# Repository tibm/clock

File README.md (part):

# Wooden Smart Clock — Hardware Specification

> Living spec for a high-quality, low-power desk alarm clock: a **walnut cube (~120 mm)** with an **aluminum front plate**, a centered **Ø~90 mm MCU-driven analog dial behind glass** (aluminum hands on walnut, 12 black hour dots, no numerals), a row of **5 RGBW status LEDs** under the dial, and one **aluminum knob (rotate + press)** centered on the top face.

> 🔩 **Manufacturing constraint — HAND-SOLDERABLE PARTS ONLY.** The bare PCB is fab'd externally; **every part is hand-soldered with an iron.** No **QFN / DFN / WSON / BGA / WLP / LGA** silicon sits bare on the board — every active IC is a **leaded/gullwing** package (SOIC / SOP / SSOP / TSSOP / **HTSSOP** / **MSOP** / SOT-23) or a **castellated/edge module**. The two power parts (amp `TAS5760M`, charger `LT3652`) are HTSSOP/MSOP **PowerPAD** — leads iron-solderable, belly pad on a thermal-via array (back-side hot-air optional). Functions that *only* exist leadless → **pre-made breakout modules** (env/MEMS sensors — **BME688, TSL2591, BNO085** as I²C Qwiic/STEMMA boards; or a custom SMT daughterboard — **built: [`kicad-sensor/`](kicad-sensor/), `SENSE v0.2`**, §8) or **dropped** (fuel gauge → ESP32 ADC). **Passives ≥ 0603** (0402 min); connectors hand-solderable (through-hole / wide-pad SMD: USB-C, FPC/ZIF, JST, SD cage). **This grows the PCB — accepted.**

**Status:** v0.19 draft · **Owner:** you (FW/HW) · **Last updated:** 2026-07-19 · **What is left to build: [`TODO.md`](TODO.md)** · clock ⇄ app protocol: [`app/PROTOCOL.md`](app/PROTOCOL.md)

**Changelog**
- v0.19 — **Product redesign: walnut cube + aluminum face — display dropped, NeoPixel status/face LEDs + top-knob UX added (2026-07-19).** New form (§3): perfect **walnut cube ~120 mm** (size flexible, larger eases manufacturing), all faces wood except an **aluminum front plate** (cube − 10 mm in W/H, flush-centered → **5 mm wood reveal**) with a **centered Ø~90 mm dial opening** behind glass — **aluminum hands over a walnut dial**, no numerals, **12 black hour dots**; below the opening, **5 status-LED holes + icons** (Lucide-style `bell`, `alarm-clock`, `clock`, `volume-1`, `battery`); an **aluminum knob (rotary + push)** perfectly centered on the top face; wake light, speaker openings and USB port on the **back**. Consequences: **(1) Sharp LS032B7DD02 + FH34 FPC connector dropped** (§4; their datasheets stay in [`/datasheet`](datasheet/) for possible future reuse) — SPI2 is now **microSD-only**, software-VCOM notes moot, `LCD_DISP`/`LCD_CS` freed. **(2) Panel-LED string dropped** (Cree CLM3C ×≤12 + its AO3400A + one LEDC channel recovered) → **7× SK6812 RGBW NeoPixels on the PCB** ([Adafruit 2758](https://www.digikey.com/en/products/detail/adafruit-industries-llc/2758/6134706), 10-pack $5.95): **5 status + 2 dial-illumination**, chained on the **5 V rail** (works on battery) behind **one data GPIO (IO7 → RMT)** through an **SN74AHCT1G125 3.3→5 V buffer** ([DigiKey 376028](https://www.digikey.com/en/products/detail/texas-instruments/SN74AHCT1G125DBVR/376028), $0.14). **(3) UI = single knob**: Bourns **EM14A0D-C24-L064S** **optical** encoder (**no detent, 64 CPR**, integral push switch, **5 V** opto-ASIC, [DigiKey 954403](https://www.digikey.com/en/products/detail/bourns-inc/EM14A0D-C24-L064S/954403), $34.00) under a Kilo **OEJNI-90-1-5** machined aluminum knob (Ø23.5 mm, 1/4″ bore + set screw = the encoder's 1/4″ flatted shaft, [DigiKey 5970396](https://www.digikey.com/en/products/detail/kilo-international/OEJNI-90-1-5/5970396), $13.43), off-board on J10 (JST **ZH** 1×06 B6B-ZR incl. **+5 V** — same family + pre-crimped A06ZR cable as the sensor board) → **A/B are 5 V outputs → 100k/200k dividers → IO47/48 (PCNT)**, **ENC_SW moved MCP23017 → host IO17** (freed by the display) for a tight-debounce interrupt; **rear tactiles BTN1–3 dropped**, one **radio-disable toggle** remains on the expander (GPA3) via **J11** (JST ZH 1×02). **(4) USB-C receptacle → vertical GCT USB4160-03-0230-C** (24-pin USB 3.2 Gen2 vertical, of which only the **USB 2.0 subset** — VBUS/GND/**CC/D±** — is wired, SS pads unconnected → native USB-JTAG + 15 V PD intact; [DigiKey](https://www.digikey.com/en/products/result?keywords=USB4160-03-0230-C), **$1.22, 5,753 in stock**, active) standing on the PCB, port exits the back wall directly — **USB4105 + Adafruit 6069 panel extension dropped**; footprint adapted into `kicad/clock.pretty` from the user-supplied vendor CAD file. *(Vetting trail: **USB4140** rejected = 6-pin power-only, no D±; **UJ20-C-V-C-1** rejected = legs/layout specified for a 0.8 mm PCB; **UJ20-C-V-C-2** (TH, $0.95) was briefly primary but is backorder-only; **USB4145-03-0170-C** ($1.05) remains a same-land-family 16-pin alt.)* **(5) Orientation-awareness (R14) retired** (the cube is fixed upright; LIS3DH stays for tap-to-snooze). Unchanged: wake COB (12 V, plugged-only), audio chain, charger + battery safety, sensors, homing, steppers. Schematic (`kicad/`) regenerated; docs synced.
- v0.18 — **Protector re-picked (AP9101C went NRND/obsolete) → HYCON HY2111-GB** (SOT-23-6, OV 4.28 V / OD 2.90 V, pin-arrangement-identical → same nets; support values per its datasheet: R VDD 330 Ω→**100 Ω**, R CS 2.7 k→**2 kΩ**; AOSD32334C dual-FET unchanged). Quality single-qty alternatives (ABLIC S-8261ABMMD, Nisshinbo R5478N) are reel-only/no-stock at DigiKey → HY2111-GB sourced **LCSC C82747** (off-DigiKey like the CH224K). **X40.879 mounts directly on the PCB**: custom KiCad footprint + symbol drawn from the factory STEP + pinout figure (8 solder pins, Ø10 shaft clearance hole, both shafts pass through the board); **J4 stepper connector dropped**. **USB-C port moved to the enclosure wall** via the Adafruit **6069** panel-mount **extension** ([DigiKey 25897275](https://www.digikey.com/en/products/detail/adafruit-industries-llc/6069/25897275), ~$4.50) — the on-board **USB4105** receptacle + CH224K stay unchanged (a passive C-plug→panel-C-jack passthrough keeps CC/PD intact; the resistor-equipped Adafruit 6153 pigtail was rejected — its built-in 5.1 kΩ CC pull-downs would break the 15 V PD contract). Datasheets: `battery_protector_ap9101c.pdf` → `battery_protector_hy2111.pdf`. Schematic (`kicad/`) regenerated; docs synced.
- v0.17 — **Homing sensor re-picked: Everlight ITR8307 (went unavailable) → onsemi QRE1113.** Same reflective **phototransistor with analog output → 1 ADC pin**, so it drops into the **same 150 Ω ballast / 10 kΩ load network** unchanged (§5, [`power_values.md`](power_values.md)); no firmware or pin-map change. Trade-off: the QRE1113 is **larger (≈3.6×2.9×1.7 mm** vs the ITR8307's 3.4×1.5×1.1 mm) → a marginally bigger dial hole — still far smaller than the dropped **TCND5000** (6×4.3×3.75 mm). Through-hole gull-wing `QRE1113` (SMD `QRE1113GR` alt), trivially hand-solderable, **DigiKey 2175990 (~$0.76)**. Synced §5/§8/§16b + block diagram + [`datasheet/README.md`](datasheet/README.md) (`sensor_homing_optical_itr8307.pdf` → `sensor_homing_QRE1113-D.PDF`).
- v0.16 — **LED 12 V source resolved · MCP23017 IO expander added · pin-level map (`esp32.md`) + schematic values (`power_values.md`) · backup mode / TCO / VCOM decided.** LED: **no barrel jack** — the wake COB runs off the shared **TPS55340 12 V boost, plugged-only**; on battery the amp PVDD auto-drops to the **5 V rail via an LTC4412 mux** (quieter alarm) and the 5 V panel LEDs stay on (§9/§10, [`led.md`](led.md)). **Added the Microchip MCP23017** I²C IO expander (SOIC/SSOP-28) on the shared bus to offload slow/static lines (SPK_SD, 12 V-boost EN, stepper STBY, buttons, encoder-switch, PD PG, charger CHRG/FAULT) → **net −7 host GPIO** (§6/§16b; datasheet §19). Full **pin map now in [`esp32.md`](esp32.md)** (native USB-JTAG on IO19/20, **software VCOM** with EXTMODE=L, shared display+SD on SPI2 → **32/33 module pads**), and **per-converter passive/FB/comp values in [`power_values.md`](power_values.md)**. Decisions (2026-07-12): **backup mode = adaptive** (Wi-Fi modem-sleep → deep-sleep at low SoC); **one-shot ~77 °C TCO added** to the cell path (§10); **software VCOM** locked. Corrected the 32.768 kHz load-cap value (**~18 pF**, was mis-stated). Synced [`datasheet/README.md`](datasheet/README.md), [`power.md`](power.md), [`CLAUDE.md`](CLAUDE.md).
- v0.15 — **Sensor set consolidated to 3 parts + hand-assembly path chosen (§8).** Dropped the redundant **TMP117** (any temp sensor already gives the reading); folded **SHT45 + SGP41 → one Bosch BME688** (T + RH + pressure + VOC/gas via BSEC — one chip, one board on the bus); accel **BMA400 → LIS3DH** (no leaded accel exists; low-res tap+gravity is all we need). **Locked set = BME688 + TSL2591 + LIS3DH on both build paths → firmware identical either way.** **Build = option 2a: a STEMMA QT / Qwiic daisy-chain** of three ready Adafruit boards on one 4-wire I²C chain — **BME688 (Adafruit 5046, ~$19) + TSL2591 (1980, $6.95) + LIS3DH (2809, $4.95)** — no leadless silicon touched by the iron. **Future option 2b:** the **same** three bare chips on one small custom daughterboard, JLCPCB SMT-assembled, hand-solder only its header → smallest footprint, same part numbers → same firmware. Filed `sensor_env_bme688.pdf` + `sensor_accel_lis3dh.pdf`; removed the now-unused TMP117/SHT4x/BMA400 datasheets. Synced §8/§16a/§16b + [`datasheet/README.md`](datasheet/README.md).
- v0.14 — **Homing reworked: 2× DRV5032 Hall + hand magnets → 1× reflective optical (Everlight ITR8307).** One sensor behind a **punched dial hole**, sequential per-shaft homing, **no hand magnets** (§5). Evaluated the longer-range **Vishay TCND5000** for a >3 mm hand stand-off and **dropped it** — at **6×4.3×3.75 mm** it's ~5× the ITR8307 footprint (**3.4×1.5×1.1 mm**) → a bigger dial hole; **ITR8307 locked for the smallest hole**, hands kept **<3 mm** off the dial. Synced §3/§5/§8/§16b/§17 + [`datasheet/README.md`](datasheet/README.md) (dropped the stale Hall rows; only `sensor_homing_optical_itr8307.pdf` filed).
- v0.13 — **RTC IC dropped → ESP32-S3 RTC + 32.768 kHz crystal (no battery).** A battery-less RTC chip loses time on total power loss exactly like the S3, so it adds parts without fixing anything; the S3's internal RC oscillator alone drifts %-level over temperature (bad for a clock). Fix = a ~30¢ **32.768 kHz watch crystal** on XTAL32K (GPIO15/16) → ±~20 ppm ≈ 1.7 s/day, disciplined by **SNTP**. On loss of USB **and** the 18650, time is lost → re-sync on boot with a clock animation (accepted). Removed the RV-3028-C7/DS3231SN row + datasheet; §8, §16, §17, §6c synced.
- v0.12 — **Sensors, display connector & RTC finalized to precise parts + datasheets** ([`/datasheet`](datasheet/) rows 11–16): display FPC → **Hirose FH34SRJ-10S-0.5SH** (10-pin 0.5 mm ZIF, the panel spec's own recommended mate, on-board); T/RH → **SHT45** (±0.1 °C / ±1 %RH, replaces SHT40) + optional dedicated **TMP117** (±0.1 °C); light → **TSL2591** (188 µlx–88 klx, weak-light, replaces VEML7700); accel+orient → **BMA400** (now datasheeted); RTC **kept = RV-3028-C7** (ULP 45 nA) / **DS3231SN** (SOIC-16, on-board) — the S3's internal RTC dies on full power loss, so a backed-up RTC gives instant-correct hands at cold boot + holdover. Production BOM (§16b), §8 sensor table, and [`datasheet/README.md`](datasheet/README.md) synced; leadless sensors ride on I²C breakouts, the FPC connector is on-board.
- v0.11 — **Hand-solderable parts only (hard mfg constraint):** every bare-PCB IC is now a leaded package — no QFN/DFN/BGA/LGA. Swaps: amp **TAS5825M (VQFN) → TAS5760M** (HTSSOP-32, I²S+I²C; HPF/limiter DSP moves to firmware); driver **2× DRV8835 (WSON) → 2× TB6612FNG** (SSOP-24); PD **STUSB4500 (QFN) → CH224K** (ESSOP-10, resistor-set, off-DigiKey); charger **BQ25628E (WQFN) → LT3652** (MSOP-12E buck, BAT-node power-path, resistor-set 4.05 V + NTC + timer — no I²C, single-window temp); **fuel gauge MAX17048 (µDFN) dropped → ESP32 ADC**; protector **LC05111 (DFN) → S-8261 (SOT-23-6) + AO4800 dual-FET (SO-8)**. Leadless-only env sensors → **I²C breakout modules**. New top-of-file mfg note; datasheets swapped in [`/datasheet`](datasheet/); board grows — accepted.
- v0.10 — **Power/safety simplified (Option A)**: buck-boost **BQ25792 → BQ25628E** (1-cell buck charger, integrated FETs — buck is enough since input always > 1S cell); independent **cell protector = onsemi LC05111** (integrated FET) + **reverse-polarity P-FET** + NTC/JEITA + TVS = **double-redundant, industry-standard for 1S**. Dropped BQ29700+FETs, **secondary OVP, one-shot TCO, PPTC** (over-engineering for a single cell). Datasheets added (STUSB4500, BQ25628E, MAX17048, LC05111); `power.md` now has a **How-to-use / bring-up** section. Power subtotal ~$23 → ~$15.
- v0.9 — **Power tree locked** ([`power.md`](power.md)): **USB-PD sink (STUSB4500, 15 V)** → **BQ25792** buck-boost charger/path (+ MAX17048), 1S. Rails 3.3 / 5 / 12 V-audio-boost / 15 V-VBUS-LED. Battery = **user-supplied 18650 in a holder, Li-ion ONLY (labeled)**; **48 h backup**; health-cap ~80 %. **Mandatory board safety for any 18650**: reverse-polarity (LM74700-Q1), primary PCM (BQ29700+FETs), redundant secondary OVP, PPTC + thermal cutoff, NTC/JEITA, TVS, FR barrier — triple-redundant overcharge, layered over-discharge. Charger BQ25185 → **BQ25792**; §10/§16/§17 updated.
- v0.8 — **Amp locked = TI TAS5825M** (I²S + I²C closed-loop Class-D w/ DSP), PBTL mono into the 4 Ω DMA58-4: PVDD 5 V for ~3 W, optional ~12 V boost for ~8–12 W; DSP loads a ~150–180 Hz high-pass + limiter to protect the 2 mm-Xmax driver. MAX98357A demoted to simple/no-DSP alt. **Driver confirmed = 2× TI DRV8835** (dual H-bridge each; VM 5 V for full torque, VCC 3.3 V; PHASE/ENABLE with PWM microstep → 8 GPIO). Full datasheets added to [`/datasheet`](datasheet/); [`datasheet/README.md`](datasheet/README.md) now carries a **System IO & power domains** table (rails + per-part GPIO/voltage).
- v0.7 — **Speaker PC68-4 → Dayton DMA58-4** (2″ dual-magnet full-range — the driver we actually have a datasheet for) → smaller driver relaxes body depth to **≥45–60 mm / ~100–250 cc** chamber (optional **DMA58-PR** passive radiator for bass). **Movement locked = Juken X40.879**: its datasheet is a short **pinout addendum** that defers to the **X27 base spec** for torque/current/dimensions — both now in [`/datasheet`](datasheet/). Added the **full Sharp LS032B7DD02 device spec** (replaced the marketing brief); corrected display **active area → 42.67 × 68.07 mm** and **power → 30 µW hold / 250 µW update @ 5 V (VDD 4.8–5.5 V)**; **X40.879 price → ~$14** (was ~$25, DigiKey). Datasheets summarized in [`datasheet/README.md`](datasheet/README.md).
- v0.6 — **Split-face locked as THE design**: circular MCU-driven analog clock (~75 mm) + reflective monochrome info panel (**Sharp LS032B7DD02**). **Single MCU** (ESP32-S3). New **orientation awareness** (R14): flat (clock left / display right) ↔ standing (clock top / display bottom), accel-sensed; MCU rotates the display and re-references the analog "12". Movement re-picked for 75 mm → **Juken X40.879** (DigiKey) + external Hall homing. Motor driver **DRV8833 → DRV8835** (DRV8833 is NRND). Backlight subsystem removed (reflective display). Shopping list moved **Mouser → DigiKey**. Sections renumbered consecutively; wide color bar-TFT demoted to *superseded*.
- v0.5 — locked **Dayton PC68-4** speaker; added **Juken X10.506** + more movements; new requirement **R12** (MCU sets/adjusts analog time → sweep-quartz demoted).
- v0.4 — added **speaker comparison** and the **analog-movement comparison** for the split-face option.
- v0.3 — added **ESP32-S3** single-chip path + firmware libraries, **audio sizing**, internal packaging notes, and a distributor-linked shopping list.
- v0.2 — display moved E-Paper → fast **bar TFT** (NHD-3.9); MCU → STM32U5 + ST67W611M1, with ESP32-S3 as single-chip alt.
- v0.1 — initial spec (EPD + nRF5340).

---

## 1. Requirements (source of truth)

| # | Requirement | Primary approach (see §) |
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
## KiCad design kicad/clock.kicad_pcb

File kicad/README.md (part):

# Wooden Smart Clock — KiCad schematic + PCB

KiCad 10 schematic on **one A1 page**, organised like `../block_diagram.drawio`
(⚠ the drawio still shows the pre-v0.19 display-era design):
power flows along the left, MCU in the centre, peripherals on the right.
Open **`clock.kicad_pro`**. The sheet is **generated** by the Python code in
`gen/` (see *Regenerating* below) — edit the block files, not the `.kicad_sch`.

**`clock.kicad_pcb`** (110×110mm, 4-layer) is likewise generated —
by `gen/pcb_build.py`, run under KiCad's own bundled Python (`pcbnew`
scripting), not by hand in the PCB editor. **v3 (2026-07-23)**: full
per-part functional placement (every part hand-seeded at the pins it
serves + bounded clearance relaxation + locality proof) + stackup + GND
zones + keepouts + net assignment + collision-avoiding silkscreen;
routing is not done. See [`PCB_NOTES.md`](PCB_NOTES.md) for the placement
rationale, constraint checklist, and verification results.

## Page map

| Region | Blocks |
|---|---|
| left | POWER IN (vertical USB-C + CH224K) → CHARGER (LT3652) → BATTERY (18650 + HY2111/AOSD32334C + TCO) |
| mid-left | RAILS 5 V→3V3 · 12 V boost (plugged-only) · LED (wake drivers) · NEOPIXELS (7× SK6812) |
| centre | MCU (ESP32-S3) · SENSORS + QRE1113GR homing · IO EXPANDER + KNOB (EM14) + J11 toggle |
| right | STORAGE (microSD, SPI2) · AUDIO (TAS5760M + PVDD mux) · MOTOR (2× TB6612) |

## Wire / label conventions
- **Wired:** all block-internal circuitry; the power chain
  (VBUS → LT3652 → VBAT → both boosts); the **+12 V run** to the wake-LED
  connector and the audio PVDD mux; all MCU buses — SPI (microSD),
  I2S (amp), 8× MCPWM (motor drivers), knob A/B, expander INT; the
  SK6812 daisy-chain.
- **By name:** GND / +3V3 / +5V / VBAT / PVDD power taps, the multi-drop I²C
  bus, the MCP23017 slow fan-out (`PD_PG`, `CHRG`, `FAULT`, `SPK_SD`,
  `STEP_STBY`, `BOOST12_EN`, …), the 2 wake PWM lines, `NEOPIX_DATA` and
  `ENC_SW`.
- Off-board parts enter via connectors: J1 USB-C (**vertical** since
  2026-07-19 — port exits the back wall, no extension), J2 PROG, J3 speaker,
  J6 microSD, J7 **sensor board** (I²C + INT), J9 wake-LED strips,
  J10 **knob** (EM14 encoder + switch, top face), J11 **radio-off toggle**
  (rear), J12 **off-board status NeoPixels** (2026-07-21, see below), BT1
  cell holder. The **X40.879 stepper is on-board (M1)** since
  2026-07-17 — soldered to the PCB, shafts through a board hole (J4
  dropped). *(J5 display FPC + J8 panel string removed 2026-07-19 with the
  display; of the 7 status/dial NeoPixels, only D40/D41 — dial wash, chain
  pos 1-2 — are on-board; pixels 3-7 (status row) wire out through **J12**,
  a 3-pin JST-PH breakout, since 2026-07-21 — see `PCB_NOTES.md`.)*
- **J10 knob connector** (reworked 2026-07-19/20 for the EM14 optical
  encoder): JST **ZH** 1×06 **B6B-ZR** — same family as J7, so ONE cheap
  pre-crimped ZH↔ZH cable type (A06ZR06ZR28H152B) serves both. The **B**
  suffix is straight-through wiring; the otherwise-identical `…152A` is
  JST's *Reversed* build and destroys the BNO085 (root README §16d).
  Pinout `1 GND · 2 +5V · 3 A · 4 B · 5 SW · 6 GND`. A/B are 5 V
  outputs → on-board **100k/200k dividers** (R111/R114, R112/R115) →
  IO47/48; SW → 10 k PU (R113) + 100 nF (C239) → IO17.
  **J11** = JST ZH 1×02 **B2B-ZR** → expander GPA3 (`RADIO_OFF`,
  MCP internal PU + IOC). J7 sensor = ZH 1×06 (pin 6 spare).
  J3 speaker / J9 wake strips stay JST PH (power).

## Custom symbols (`gen/clock_custom.kicad_sym`)
`ESP32S3_CLOCK` — WROOM-1 with **functionally grouped pins** (same pad
numbers as the stock symbol/footprint) so buses leave toward their blocks;
`TAS5760M` (DAP-32), `TPS55340`, `TPS61023`, `AOSD32334C`, **`HY2111`**
(U3 protector — same body/pin geometry as the stock `AP9101CK6` symbol it
replaced 2026-07-17, HYCON pin names OD/CS/OC), **`X40_879`** (M1 stepper,
pins 1-4 = 1e-4e external shaft, 5-8 = 1i-4i internal), `VBAT`/`PVDD`
flags, plus flattened clones of stock `extends` symbols (AO3400A, AO3401A,
2N7002, DM3AT, MCP23017, **74AHCT1G125** — U15 NeoPixel buffer,
**USBLC6-2SC6** — U16 USB ESD array, 2026-07-21) so ERC
never reports lib_symbol_mismatch. NeoPixels use the stock `LED:SK6812`
symbol (standalone, RGBW-compatible pinout).

## Custom footprints (`clock.pretty`, fp-lib-table nickname `clock`)
| Footprint | Part | Source |
|---|---|---|
| `OnSemi_QRE1113GR` | U14 homing sensor (SMD) | land pattern from datasheet p.8 (Case 100CY): 1.66×0.79 pads, 5.66 span, 2.59 row pitch |
| `Fuse_TCO_Cantherm_SDF_L10.5mm_D4.0mm_P20.32mm_Horizontal` | F1 TCO 77 °C | Cantherm SDF drawing: Ø4×10.5 body, AWG18 leads, 1.3 mm drills, ≥3 mm bend clearance |
| `Juken_X40-879_DualShaft` | M1 stepper (direct PCB mount) | factory STEP (`X40 v5`) cross-checked vs X27 base-spec Fig. 6: 4× Ø0.8 pin drills on 22.86×7.62 grid (pads 1-4 = 1e-4e), 4× Ø1.8 rim-tail drills at (±13.96, ±6.36) (pads 5-8 = 1i-4i), 3× Ø3.0 NPTH snap pegs, Ø4.6 NPTH shaft hole at (0, −6); body Ø31.5 on the far side (flip to back in layout, shafts through-board); 3D STEP in `3d/X40_879.step` (rotation/offset eyeballed — cosmetic) |
| `GCT_USB4160-03-0230-C_USB_C_Vertical` | J1 vertical USB-C | user-supplied vendor CAD footprint (`~/Downloads/KiCADv6/`), cleaned: 24 SMT pads kept verbatim; the 4 stake slots made **plated, pad `SH`** (GCT drawing 2/4 marks them Solder Area; 1.10×0.61 drill / 1.60×1.10 pad at ±4.00/±1.43 — matches the drawing exactly); pegs → NPTH Ø0.71 (right one slotted); stray Edge.Cuts/S_3 artifacts removed. Only the USB 2.0 subset is wired (16P symbol) → SS pads unconnected. ⚠ cross-check vs the GCT drawing before fab |
| `BatteryHolder_Keystone_1043_1x18650` | BT1 18650 holder (THM) | resolves the 1042(footprint)↔1043(BOM) mismatch **in favor of the 1043** (TH PC pins, DK 21.9 k stock, $2.99). Body/pegs/index copied from the stock KiCad **1042** footprint (shared molding: diagonal Ø3.45 pegs at ±27.6/∓8, Ø2.39 index at −36.13/−8); PC pins Ø1.19 on the axis at **±35.8** (catalog 2.822″ span; the stalled KiCad MR !2043 used ±36.11) with **Ø2.6 drill / Ø4.2 pad** so either reading fits. ⚠ verify vs the Keystone 1043 drawing before fab |
| *(unused, kept)* `SameSky_UJ20-C-V-C-2_USB_C_Vertical_TH` | ex-J1 candidate (TH) | drawn 2026-07-19 while the UJ20-C-V-C-2 was primary (superseded by the in-stock USB4160); kept in case the TH option returns |
| *(removed 2026-07-19)* | ~~`Hirose_FH34SRJ-10S-0.5SH…`~~ J5 display FPC | file kept in `clock.pretty` for a future display variant; no longer referenced |

## Validation (all automated in `gen/`)
- `kicad-cli sch erc` → **0 violations (clean)**. The two former "benign"
  items — LT3652 BAT (Output) ↔ VBAT PWR_FLAG and QRE1113 emitter
  (Open-emitter) ↔ GND flag — were cleared 2026-07-25 by retyping those two
  stock-symbol pins to `passive` on embed (`schlib.py` `PIN_TYPE_OVERRIDES`);
  both are electrically passive taps, so connectivity/netlist are unchanged.
- `gen/build.py` lint: no dangling wires, no body overlaps, no wires through
  symbols; junctions auto-placed with eeschema's own rules (T-points,
  pin-joins; wires broken at crossing-joins) so a GUI re-save is a no-op.
- Every symbol has a footprint (audited 2026-07-20 — including the 7
  SK6812 pixels on the stock `LED_SK6812_PLCC4` pattern and the QRE1113GR
  homing sensor); the parts without stock land patterns use `clock.pretty`
  (table above: QRE1113GR, TCO, X40.879, USB4160). Headless `kicad-cli` may
  warn `footprint_link_issues` for exactly those (it skips the project
  fp-lib-table) — eeschema resolves them fine.

### Desk-verified 2026-07-17 (was "reconcile before fab")
1. **TAS5760M bootstrap caps**: the 33 nF placeholder was **wrong** — the
   datasheet typical application (Fig. 62, DAP-32) uses **0.22 µF**;
   §9.2.2.2.3 warns deviating can cause "destructive failure".
   C180–C183 are now **220 nF**.
2. **TPS55340 compensation** (R48 2.55 k / C134 0.1 µF / C135 100 pF):
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
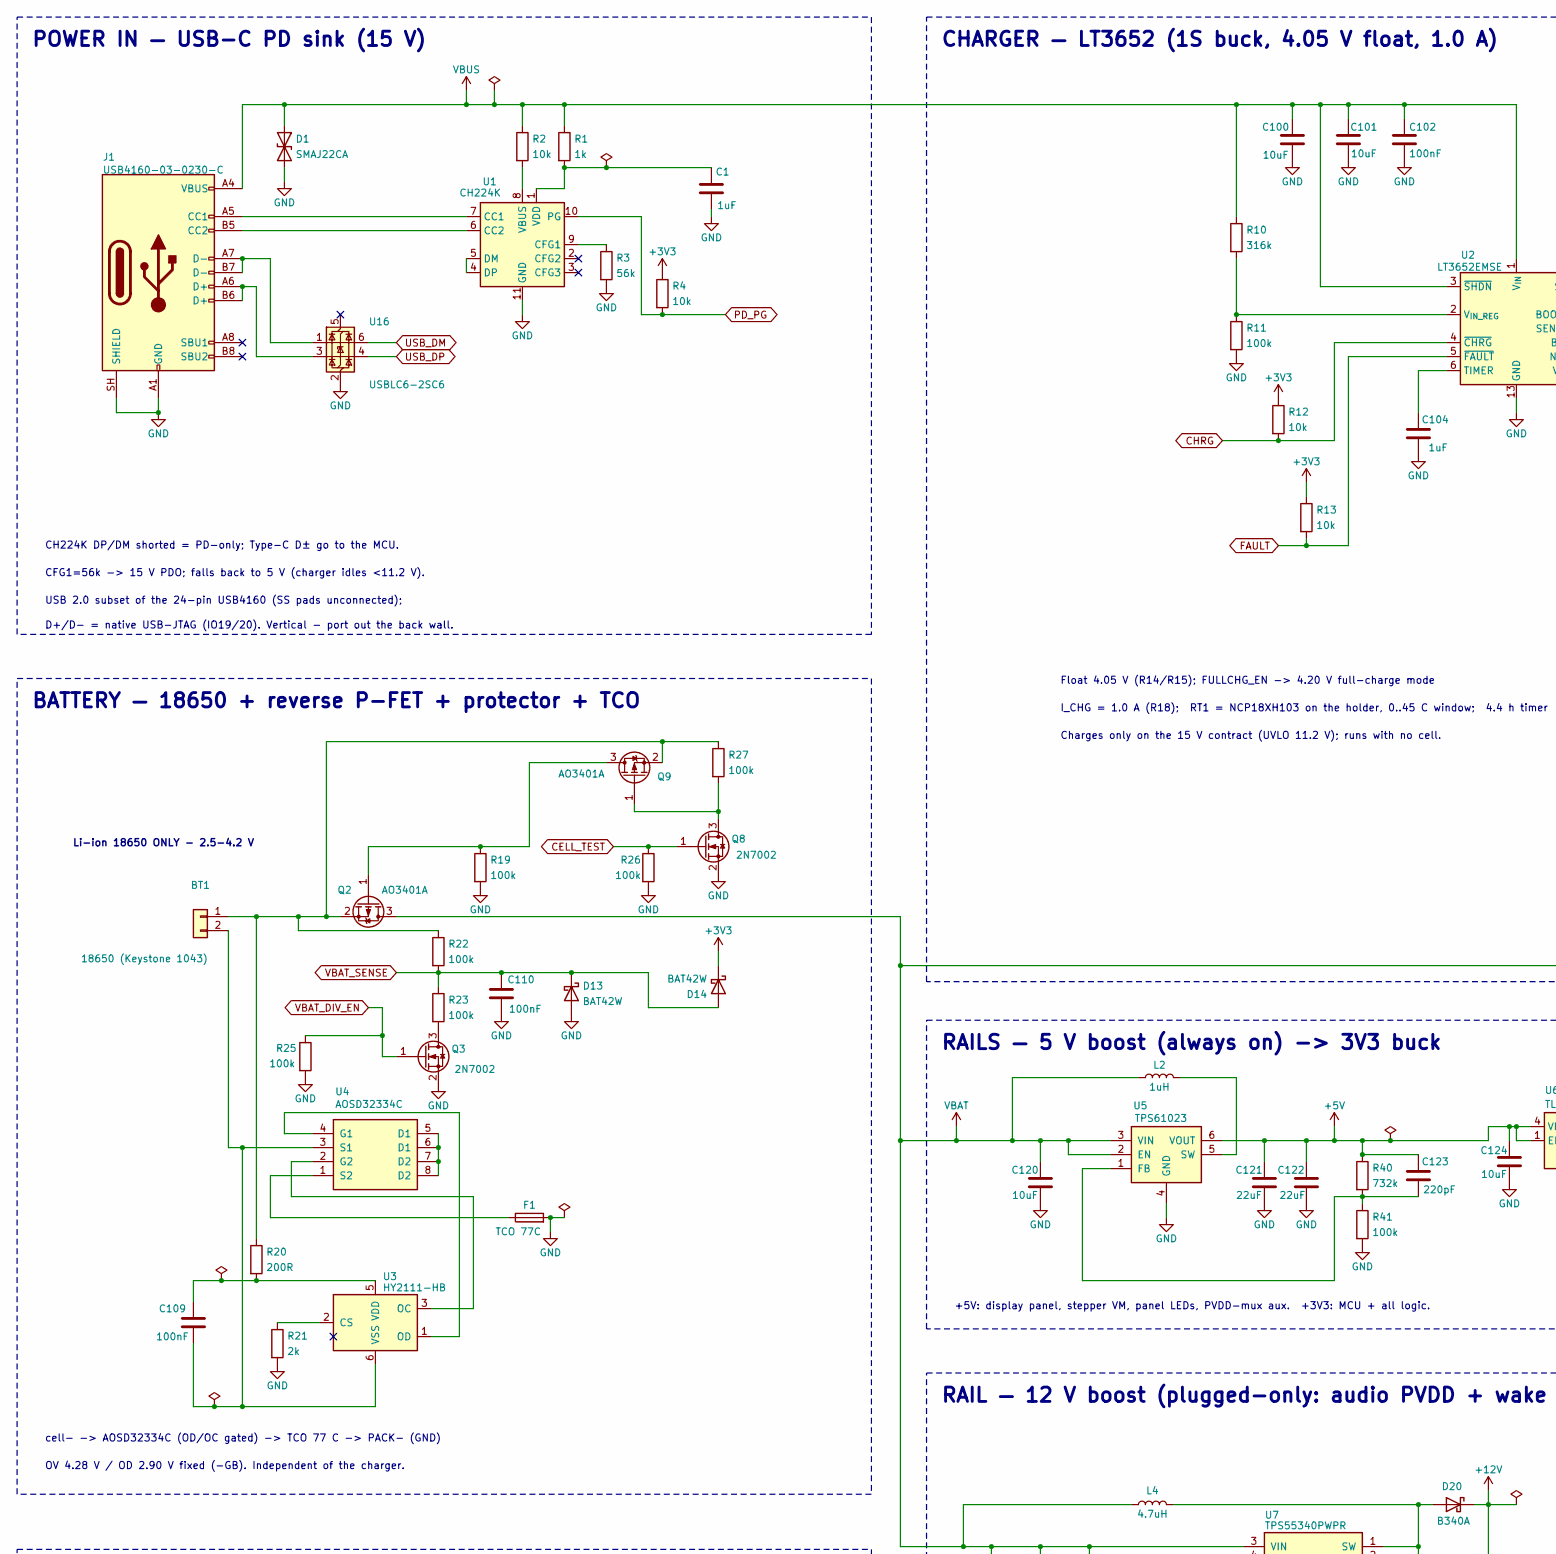
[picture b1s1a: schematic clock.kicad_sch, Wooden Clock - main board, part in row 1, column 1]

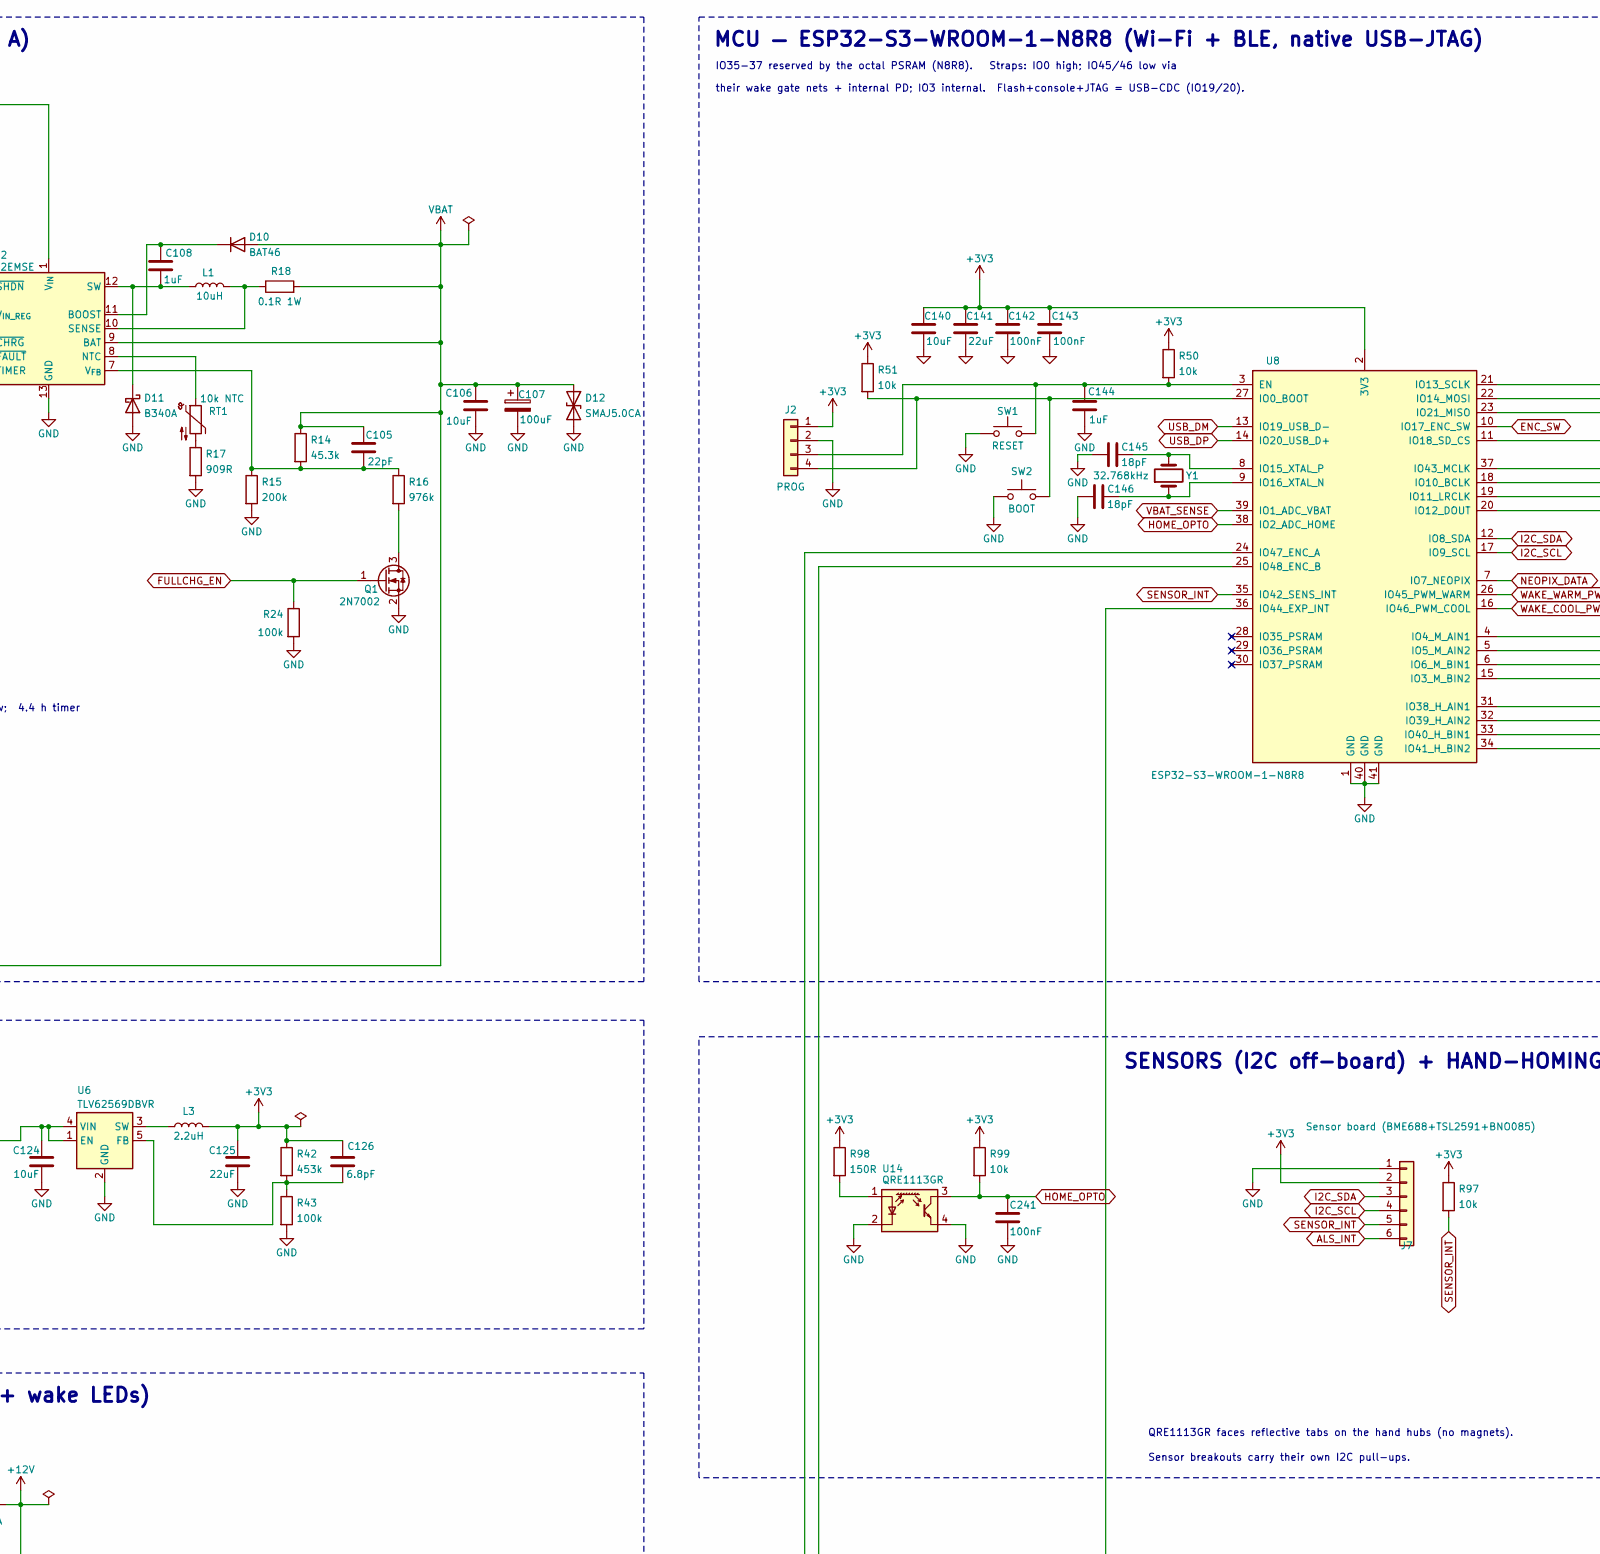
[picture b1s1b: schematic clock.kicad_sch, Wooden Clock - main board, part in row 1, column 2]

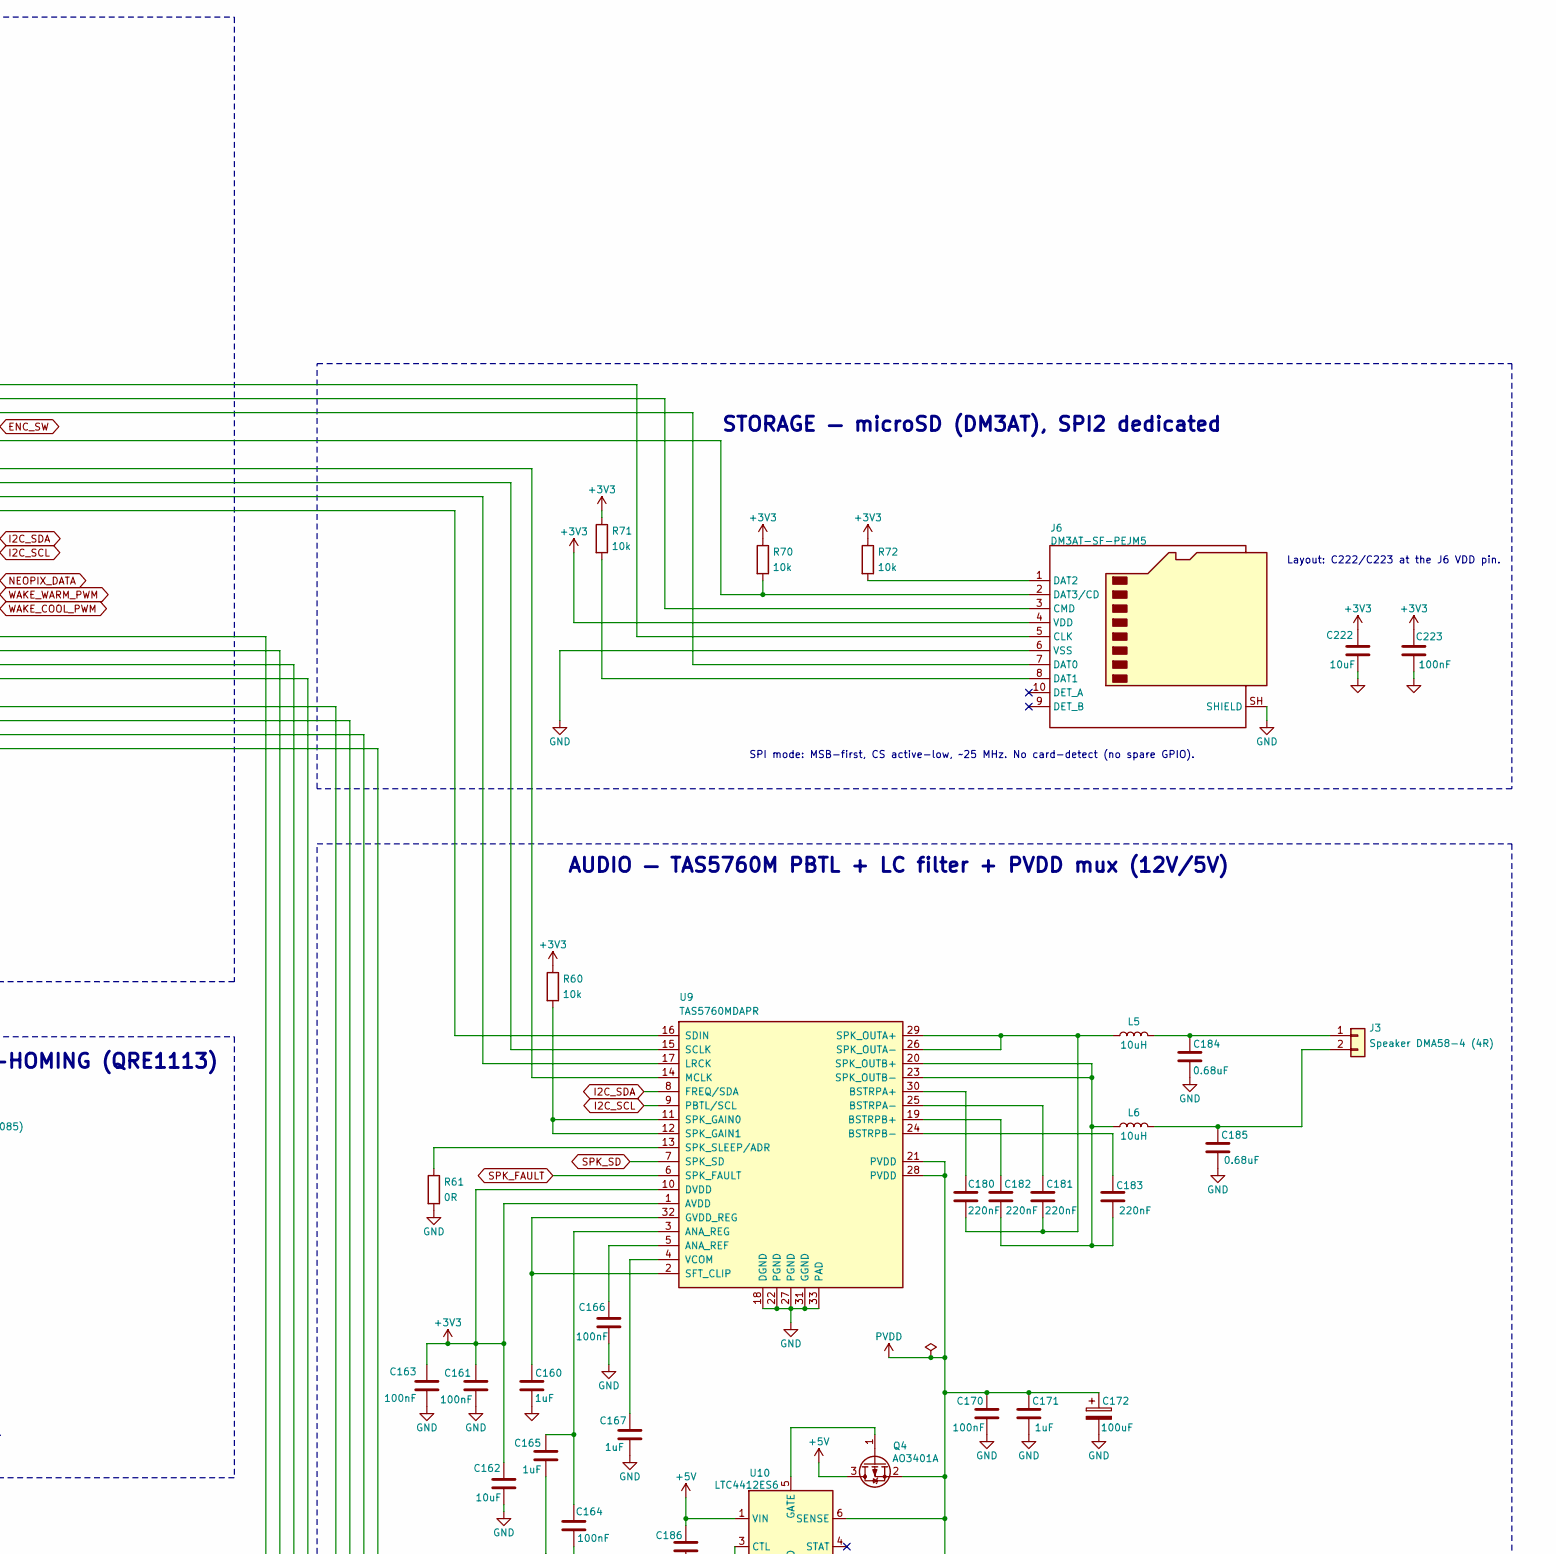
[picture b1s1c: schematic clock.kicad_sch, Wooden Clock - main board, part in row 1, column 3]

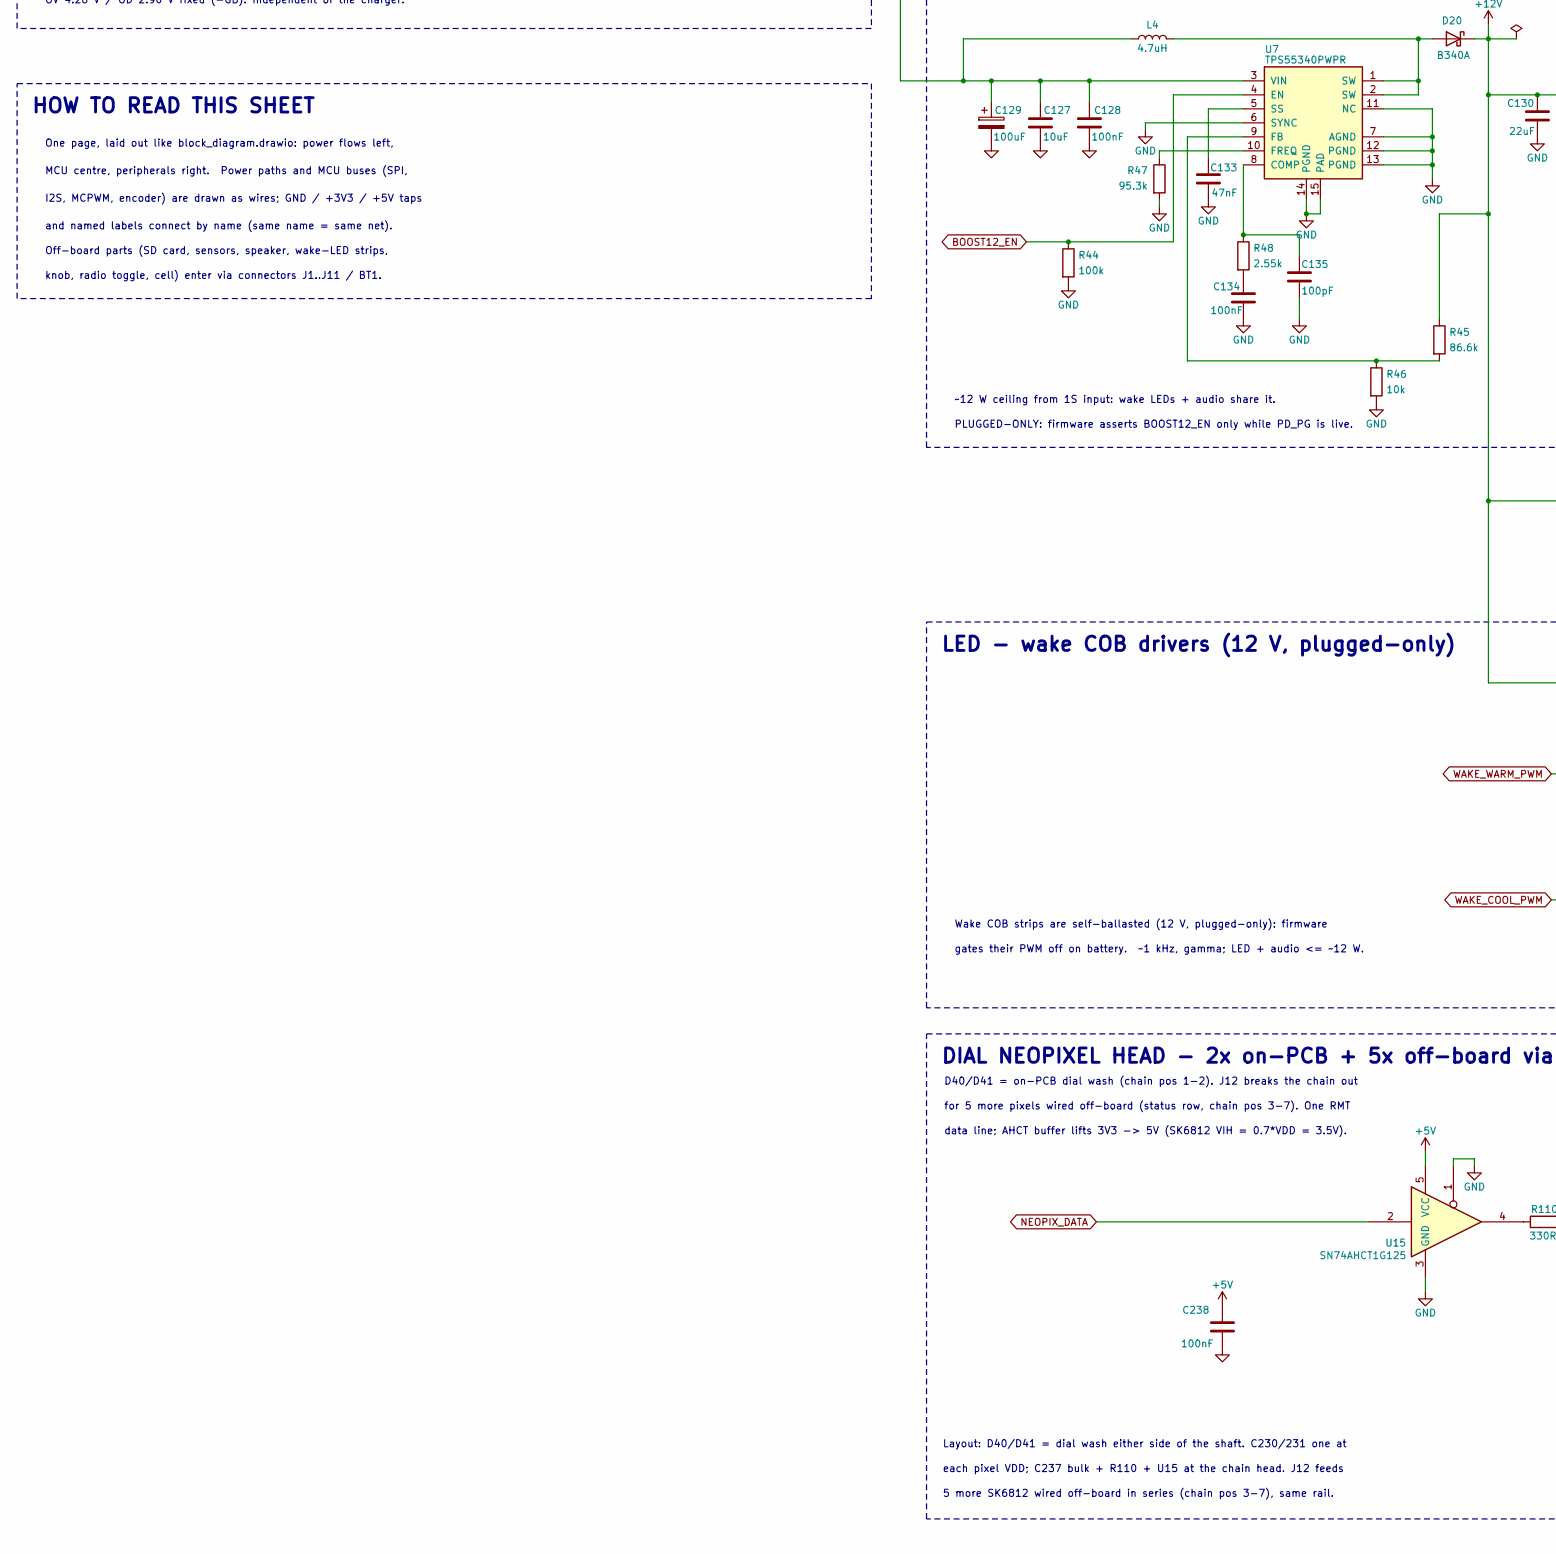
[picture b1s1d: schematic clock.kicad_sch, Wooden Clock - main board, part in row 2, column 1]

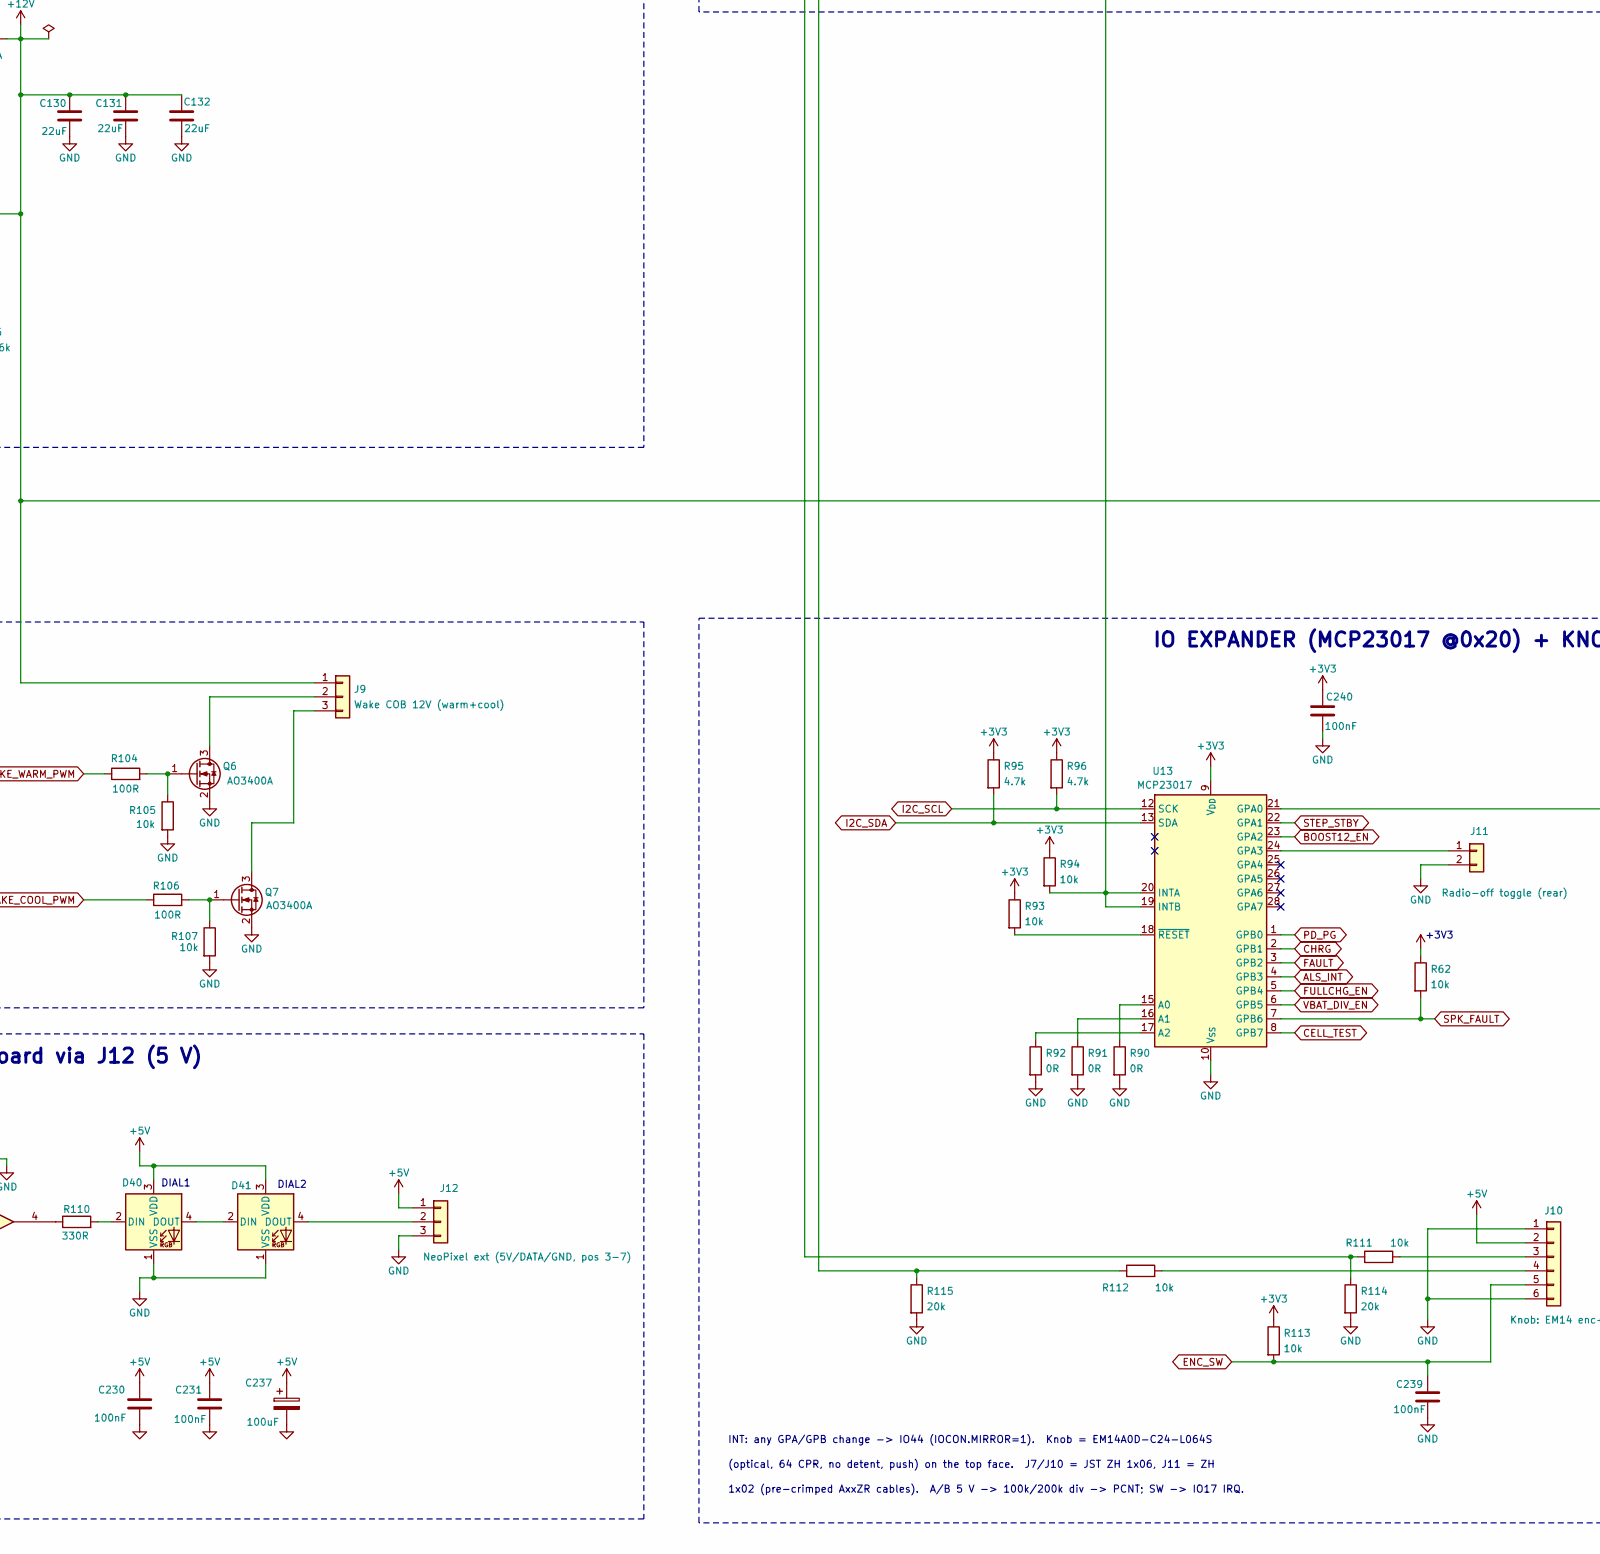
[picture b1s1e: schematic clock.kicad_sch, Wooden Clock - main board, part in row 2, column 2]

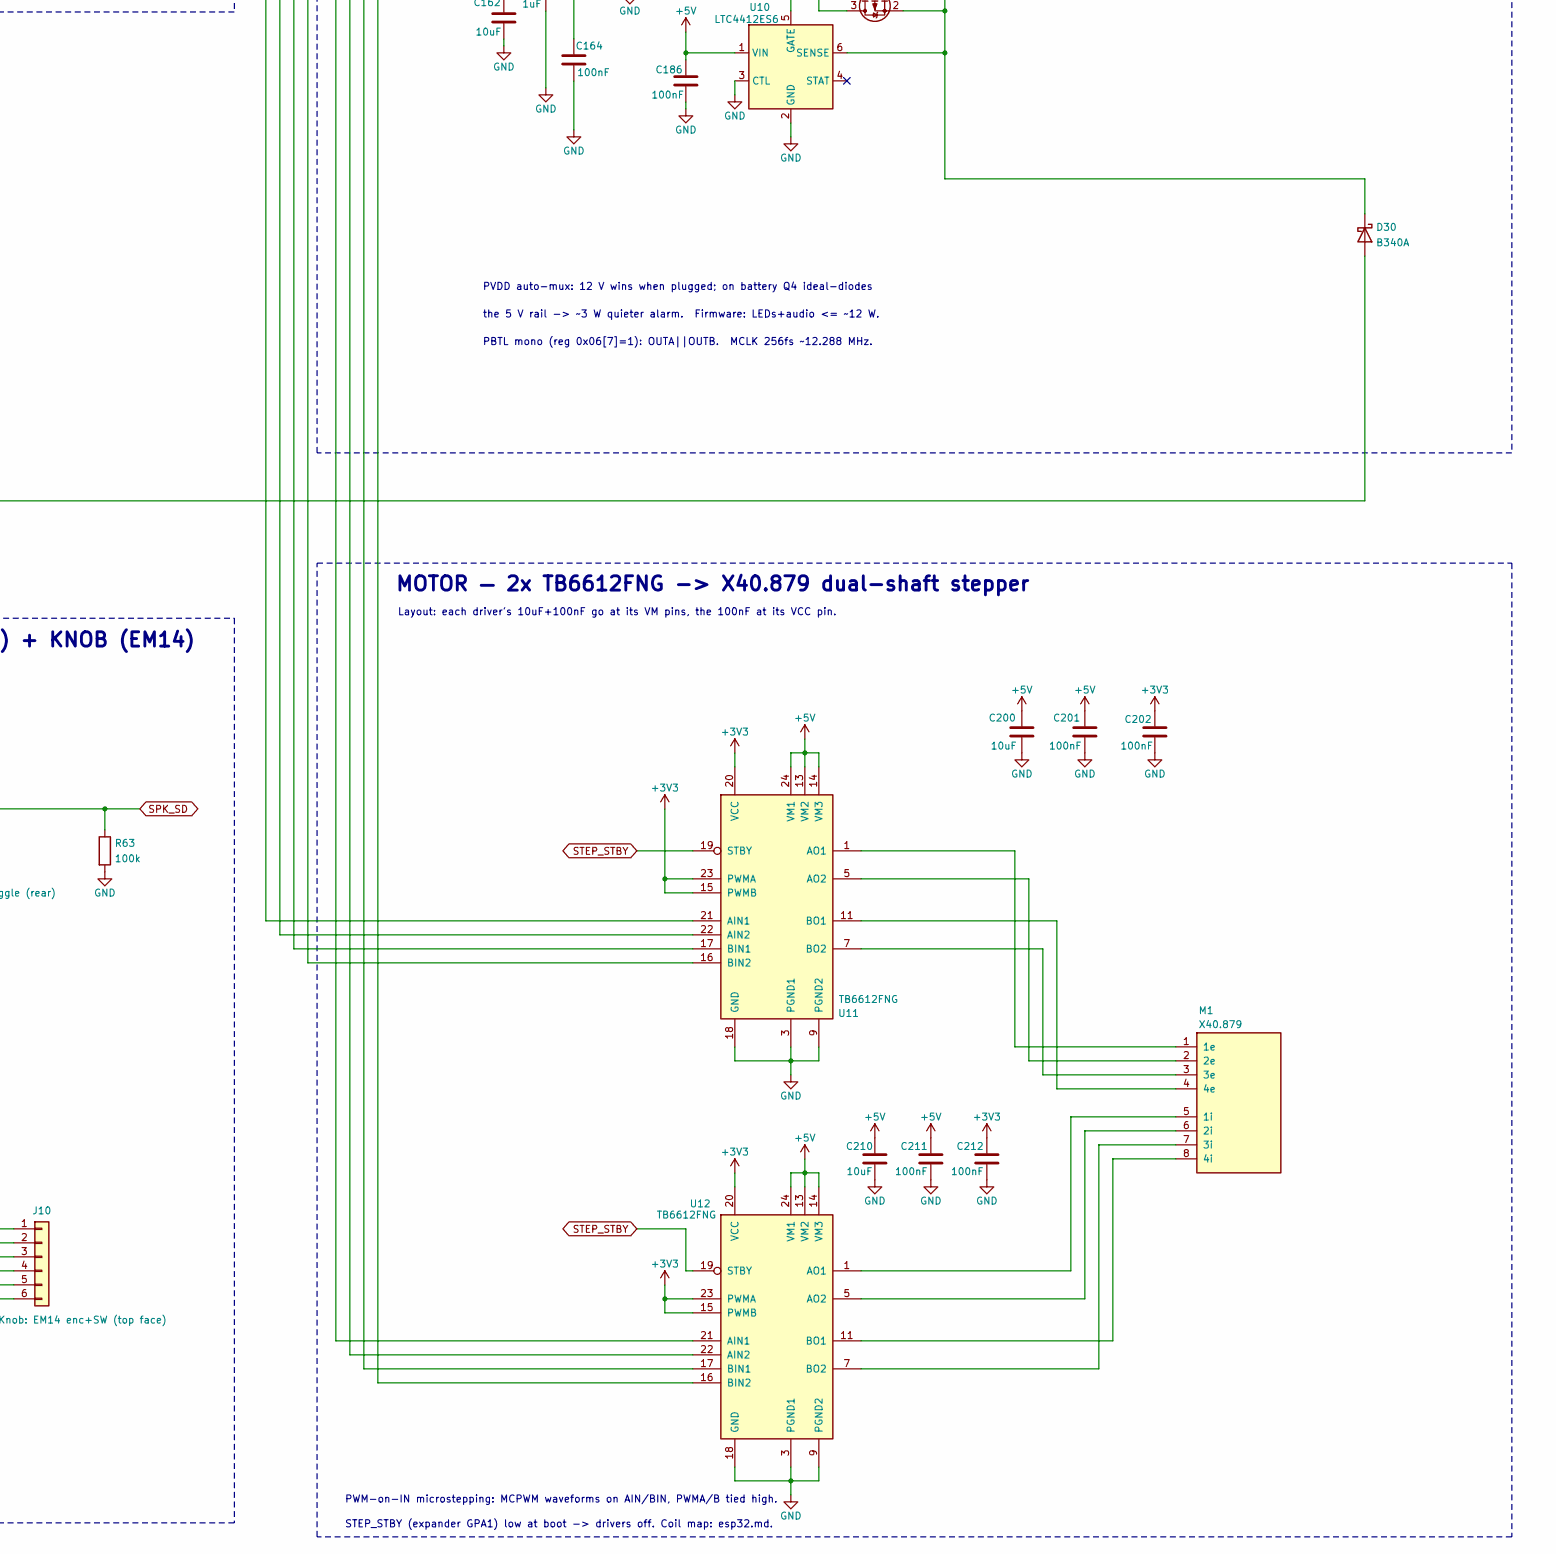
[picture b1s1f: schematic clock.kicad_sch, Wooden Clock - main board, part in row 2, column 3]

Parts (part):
BT1: 18650 (Keystone 1043); BatteryHolder_Keystone_1043_1x18650; MPN 1043
C1, C104, C108, C144, C160, C165, C167, C171: 1uF; C_0603_1608Metric; MPN CL10B105KA8NNNC
C100, C101, C106, C120, C124, C127, C140, C162, C200, C210, C222: 10uF; C_0805_2012Metric; MPN CL21A106KAYNNNE
C102, C109, C110, C128, C134, C142, C143, C161, C163, C164, C166, C170, C186, C201, C202, C211, C212, C223, C230, C231, C238, C239, C240, C241: 100nF; C_0603_1608Metric; MPN CL10B104KB8NNNC
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
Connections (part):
+3V3: C125.1, C126.1, C140.1, C141.1, C142.1, C143.1, C161.1, C162.1, C163.1, C202.1, C212.1, C222.1, C223.1, C240.1, D14.1 (K), J2.1, J6.4 (VDD), J7.2, L3.2, R4.1, R12.1, R13.1, R42.1, R50.1, R51.1, R60.1, R62.1, R70.1, R71.1, R72.1, R93.1, R94.1, R95.1, R96.1, R97.1, R98.1, R99.1, R113.1, U8.2 (3V3), U9.1 (AVDD), U9.10 (DVDD), U11.15 (PWMB), U11.20 (VCC), U11.23 (PWMA), U12.15 (PWMB), U12.20 (VCC), U12.23 (PWMA), U13.9 (V_{DD})
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
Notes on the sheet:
each pixel VDD; C237 bulk + R110 + U15 at the chain head. J12 feeds
PLUGGED-ONLY: firmware asserts BOOST12_EN only while PD_PG is live.
data line; AHCT buffer lifts 3V3 -> 5V (SK6812 VIH = 0.7*VDD = 3.5V).
SPI mode: MSB-first, CS active-low, ~25 MHz. No card-detect (no spare GPIO).
I_CHG = 1.0 A (R18); RT1 = NCP18XH103 on the holder, 0..45 C window; 4.4 h timer
MOTOR — 2x TB6612FNG -> X40.879 dual-shaft stepper
QRE1113GR faces reflective tabs on the hand hubs (no magnets).
USB 2.0 subset of the 24-pin USB4160 (SS pads unconnected);
Layout: D40/D41 = dial wash either side of the shaft. C230/231 one at
cell- -> AOSD32334C (OD/OC gated) -> TCO 77 C -> PACK- (GND)
CH224K DP/DM shorted = PD-only; Type-C D± go to the MCU.
CFG1=56k -> 15 V PDO; falls back to 5 V (charger idles <11.2 V).
CHARGER — LT3652 (1S buck, 4.05 V float, 1.0 A)
Li-ion 18650 ONLY - 2.5-4.2 V
and named labels connect by name (same name = same net).
PWM-on-IN microstepping: MCPWM waveforms on AIN/BIN, PWMA/B tied high.
SENSORS (I2C off-board) + HAND-HOMING (QRE1113)
knob, radio toggle, cell) enter via connectors J1..J11 / BT1.
DIAL1
INT: any GPA/GPB change -> IO44 (IOCON.MIRROR=1). Knob = EM14A0D-C24-L064S
D40/D41 = on-PCB dial wash (chain pos 1-2). J12 breaks the chain out
DIAL2
Charges only on the 15 V contract (UVLO 11.2 V); runs with no cell.
1x02 (pre-crimped AxxZR cables). A/B 5 V -> 100k/200k div -> PCNT; SW -> IO17 IRQ.
their wake gate nets + internal PD; IO3 internal. Flash+console+JTAG = USB-CDC (IO19/20).
RAILS — 5 V boost (always on) -> 3V3 buck
(optical, 64 CPR, no detent, push) on the top face. J7/J10 = JST ZH 1x06, J11 = ZH
DIAL NEOPIXEL HEAD - 2x on-PCB + 5x off-board via J12 (5 V)
+3V3
MCU — ESP32-S3-WROOM-1-N8R8 (Wi-Fi + BLE, native USB-JTAG)
+5V: display panel, stepper VM, panel LEDs, PVDD-mux aux. +3V3: MCU + all logic.
MCU centre, peripherals right. Power paths and MCU buses (SPI,
BATTERY — 18650 + reverse P-FET + protector + TCO
STORAGE — microSD (DM3AT), SPI2 dedicated
Layout: each driver's 10uF+100nF go at its VM pins, the 100nF at its VCC pin.
OV 4.28 V / OD 2.90 V fixed (-GB). Independent of the charger.
Sensor breakouts carry their own I2C pull-ups.
HOW TO READ THIS SHEET
I2S, MCPWM, encoder) are drawn as wires; GND / +3V3 / +5V taps
Off-board parts (SD card, sensors, speaker, wake-LED strips,
